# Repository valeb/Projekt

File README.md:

Projekt
=======

Maturaprojekt von Valetnin Bernard, 5AEL Gewerbeoberschule Meran, SJ 2013/14
Alarmanlage mit RFID-Deaktivierung

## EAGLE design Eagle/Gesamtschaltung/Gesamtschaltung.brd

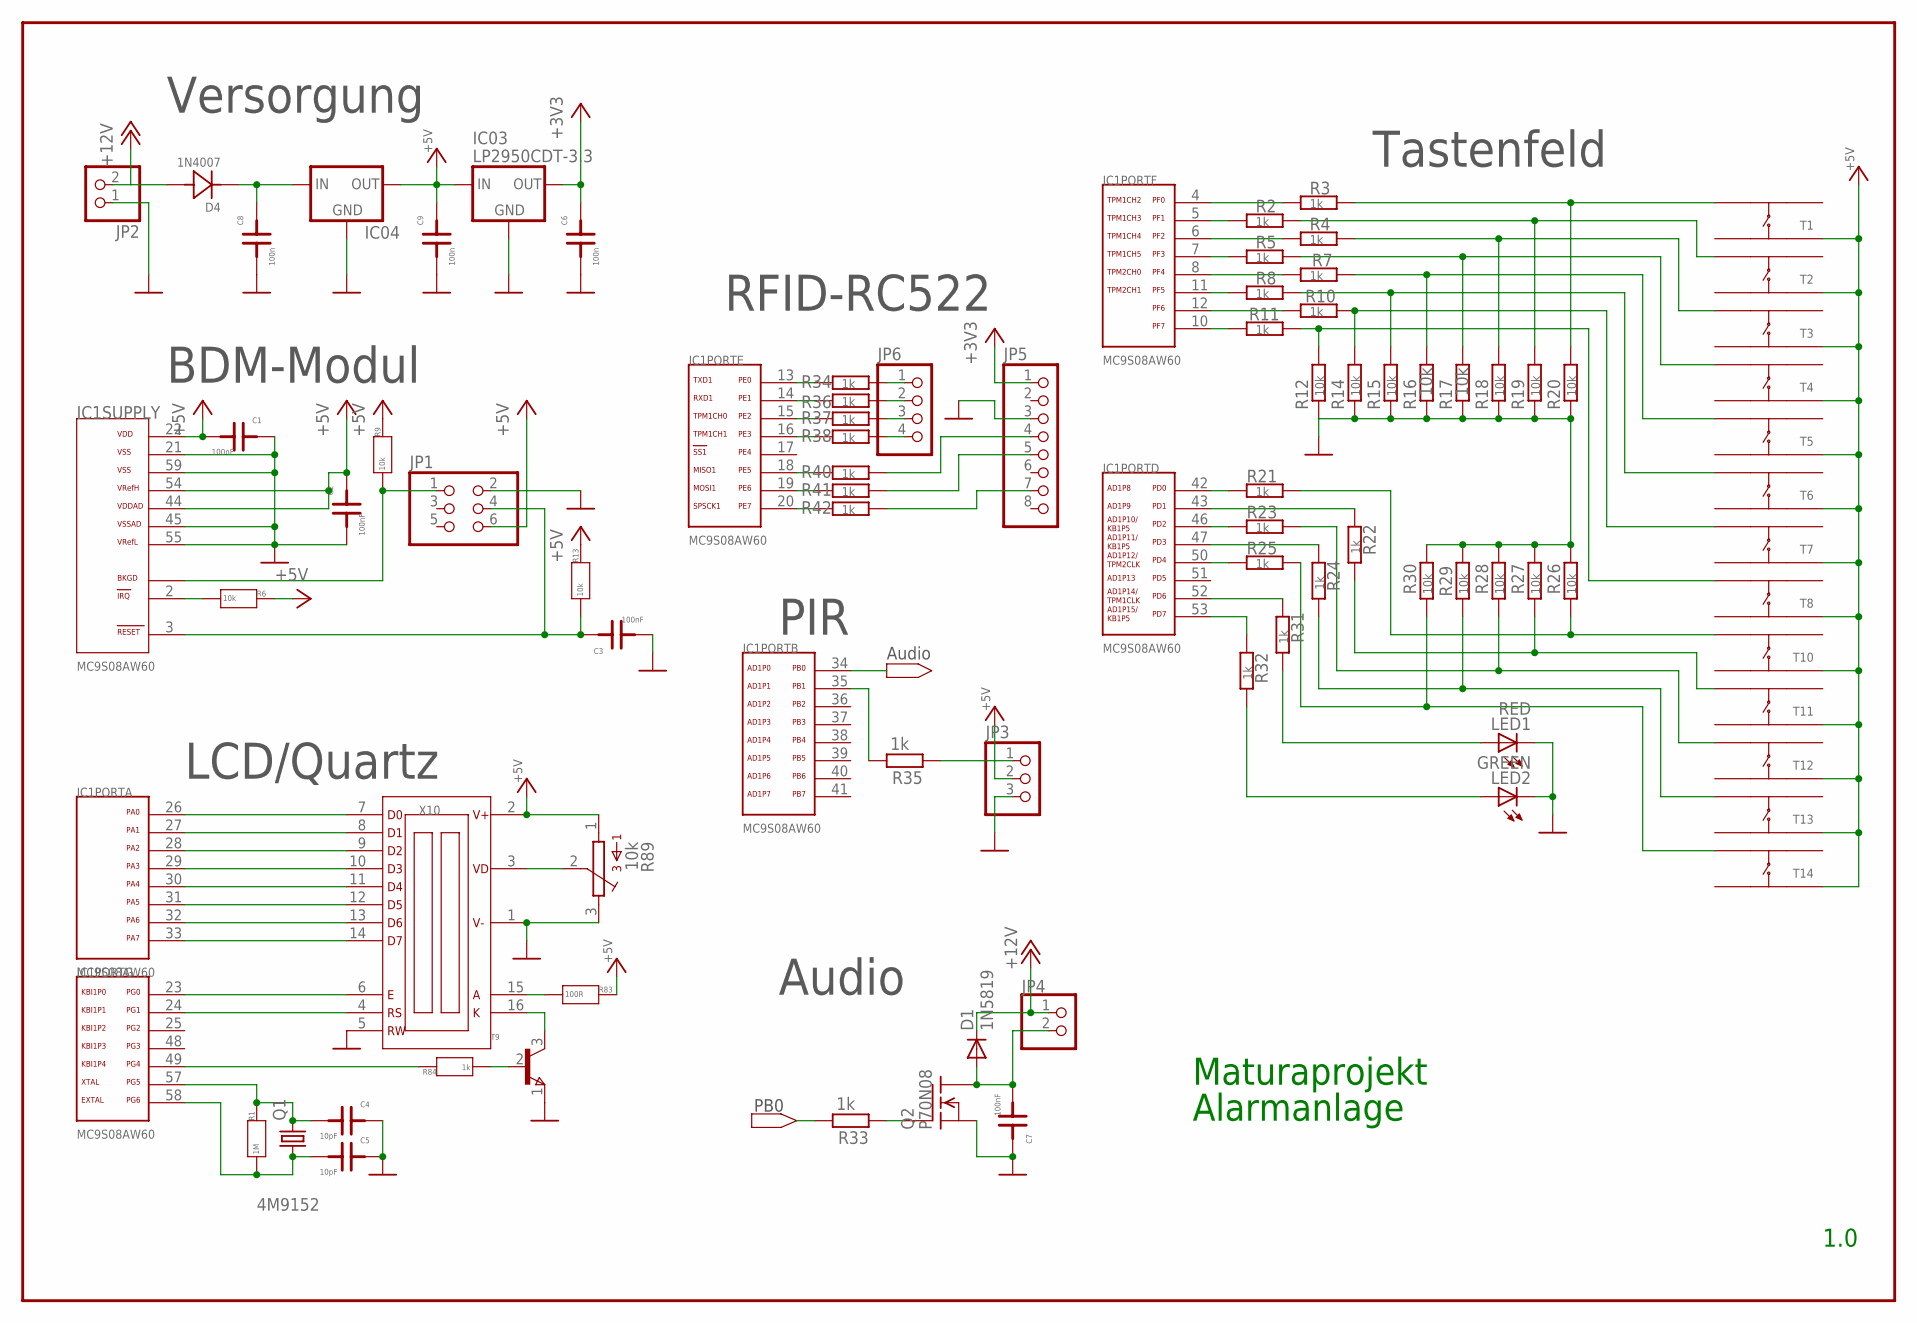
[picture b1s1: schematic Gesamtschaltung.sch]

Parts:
C1, C2, C3, C7: 100nF; 0805F
C4, C5: 10pF; 0805F
C6, C8, C9: 100n; 0805F
D1: 1N5819; DO41-10
D4: 1N4007; D400BH
IC1: MC9S08AW60; LQFP64
IC03: LP2950CDT-3.3; DPACK
IC04: 78XXS
JP1: PINHD-2X3; 2X03
JP2, JP4: PINHD-1X2; 1X02
JP3: PINHD-1X3; 1X03
JP5: PINHD-1X8; 1X08
JP6: PINHD-1X4; 1X04
LED1: RED; LED3MM
LED2: GREEN; LED3MM
Q1: 4M9152; HC49UP
Q2: P70N08; TO220
R1: 1M; 0805
R2, R3, R4, R5, R7, R8, R10, R11, R21, R22, R23, R24, R25, R34, R35, R36, R37, R38, R40, R41, R42: 1k; M0805
R6, R9, R13: 10k; 0805
R12, R14, R15, R16, R17, R18, R19, R20, R26, R27, R28, R29, R30: 10k; M0805
R31, R32: 1k; R0805
R33: 1k; 0207/10
R83: 100R; 0805
R84: 1k; 0805
R89: 10k; S63X
T1, T2, T3, T4, T5, T6, T7, T8, T10, T11, T12, T13, T14: TASTERTHT; TASTE_THT
T9: BC817; SOT-23
X10: FDCC1602E

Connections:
+3V3: C6.2, IC03.3 (OUT), JP5.1
+5V: C1.1, C2.2, C9.2, IC1.22 (VDD), IC1.44 (VDDAD), IC1.54 (VREFH), IC03.1 (IN), IC04.OUT, JP1.6, JP3.2, R6.2, R9.2, R13.2, R83.2, R89.1, T1.A1, T2.A1, T3.A1, T4.A1, T5.A1, T6.A1, T7.A1, T8.A1, T10.A1, T11.A1, T12.A1, T13.A1, T14.A1, X10.2 (V+)
+12V: D1.C, D4.A, JP2.2, JP4.1
BKGD: IC1.56 (BKGD), JP1.1, R9.1
D0: IC1.26 (PA0), X10.7 (D0)
D1: IC1.27 (PA1), X10.8 (D1)
D2: IC1.28 (PA2), X10.9 (D2)
D3: IC1.29 (PA3), X10.10 (D3)
GND: C1.2, C2.1, C3.1, C4.2, C5.2, C6.1, C7.2, C8.1, C9.1, IC1.21 (VSS), IC1.45 (VSSAD), IC1.55 (VREFL), IC1.59 (VSS2), IC03.4 (GND), IC04.GND, JP1.2, JP2.1, JP3.3, JP5.3, LED1.K (C), LED2.K (C), Q2.3 (S), R12.1, R14.1, R15.1, R16.1, R17.1, R18.1, R19.1, R20.1, R26.2, R27.2, R28.2, R29.2, R30.2, R89.3, T9.1 (E), X10.1 (V-), X10.5 (RW)
IRQ: IC1.2 (IRQ/), R6.1
LCD_LED: IC1.49 (PG4), R84.2
unnamed: C8.2, D4.K, IC04.IN
unnamed: R3.2, R20.2, T1.B2
unnamed: R2.2, R19.2, T2.B2
unnamed: IC1.42 (PD0), R21.1
unnamed: R4.2, R18.2, T3.B2
unnamed: R5.2, R17.2, T4.B2
unnamed: R7.2, R16.2, T5.B2
unnamed: IC1.46 (PD2), R23.1
unnamed: IC1.50 (PD4), R25.1
unnamed: R21.2, R26.1, T10.B2
unnamed: R8.2, R15.2, T6.B2
unnamed: R10.2, R14.2, T7.B2
unnamed: R11.2, R12.2, T8.B2
unnamed: IC1.5 (PF1), R2.1
unnamed: IC1.6 (PF2), R4.1
unnamed: C4.1, IC1.57 (PG5), Q1.2, R1.2
unnamed: IC1.43 (PD1), R22.1
unnamed: IC1.47 (PD3), R24.1
unnamed: R22.2, R27.1, T11.B2
unnamed: IC1.53 (PD7), R32.1
unnamed: IC1.7 (PF3), R5.1
unnamed: C5.1, IC1.58 (PG6), Q1.1, R1.1
unnamed: IC1.8 (PF4), R7.1
unnamed: IC1.11 (PF5), R8.1
unnamed: IC1.12 (PF6), R10.1
unnamed: IC1.10 (PF7), R11.1
unnamed: IC1.4 (PF0), R3.1
unnamed: R24.2, R29.1, T13.B2
unnamed: IC1.52 (PD6), R31.1
unnamed: R23.2, R28.1, T12.B2
unnamed: R25.2, R30.1, T14.B2
unnamed: IC1.13 (PE0), R34.1
unnamed: LED2.A, R32.2
unnamed: LED1.A, R31.2
unnamed: JP5.7, R42.2
unnamed: IC1.34 (PB0), R33.2
unnamed: JP3.1, R35.1
unnamed: JP5.5, R41.2
unnamed: JP5.4, R40.2
unnamed: Q2.1 (G), R33.1
unnamed: IC1.35 (PB1), R35.2
unnamed: IC1.14 (PE1), R36.1
unnamed: IC1.15 (PE2), R37.1
unnamed: IC1.16 (PE3), R38.1
unnamed: JP6.4, R38.2
unnamed: C7.1, D1.A, JP4.2, Q2.2 (D)
unnamed: IC1.18 (PE5), R40.1
unnamed: IC1.19 (PE6), R41.1
unnamed: IC1.30 (PA4), X10.11 (D4)
unnamed: IC1.31 (PA5), X10.12 (D5)
unnamed: IC1.32 (PA6), X10.13 (D6)
unnamed: IC1.33 (PA7), X10.14 (D7)
unnamed: IC1.20 (PE7), R42.1
unnamed: JP6.3, R37.2
unnamed: IC1.23 (PG0), X10.6 (E)
unnamed: JP6.2, R36.2
unnamed: JP6.1, R34.2
unnamed: IC1.24 (PG1), X10.4 (RS)
unnamed: R89.2, X10.3 (VD)
unnamed: R83.1, X10.15 (A)
unnamed: T9.3 (C), X10.16 (K)
unnamed: R84.1, T9.2 (B)
RESET: C3.2, IC1.3 (RST/), JP1.4, R13.1

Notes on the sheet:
Maturaprojekt
Alarmanlage
1.0
Tastenfeld
Versorgung
BDM-Modul
LCD/Quartz
PIR
RFID-RC522
Audio
PB0

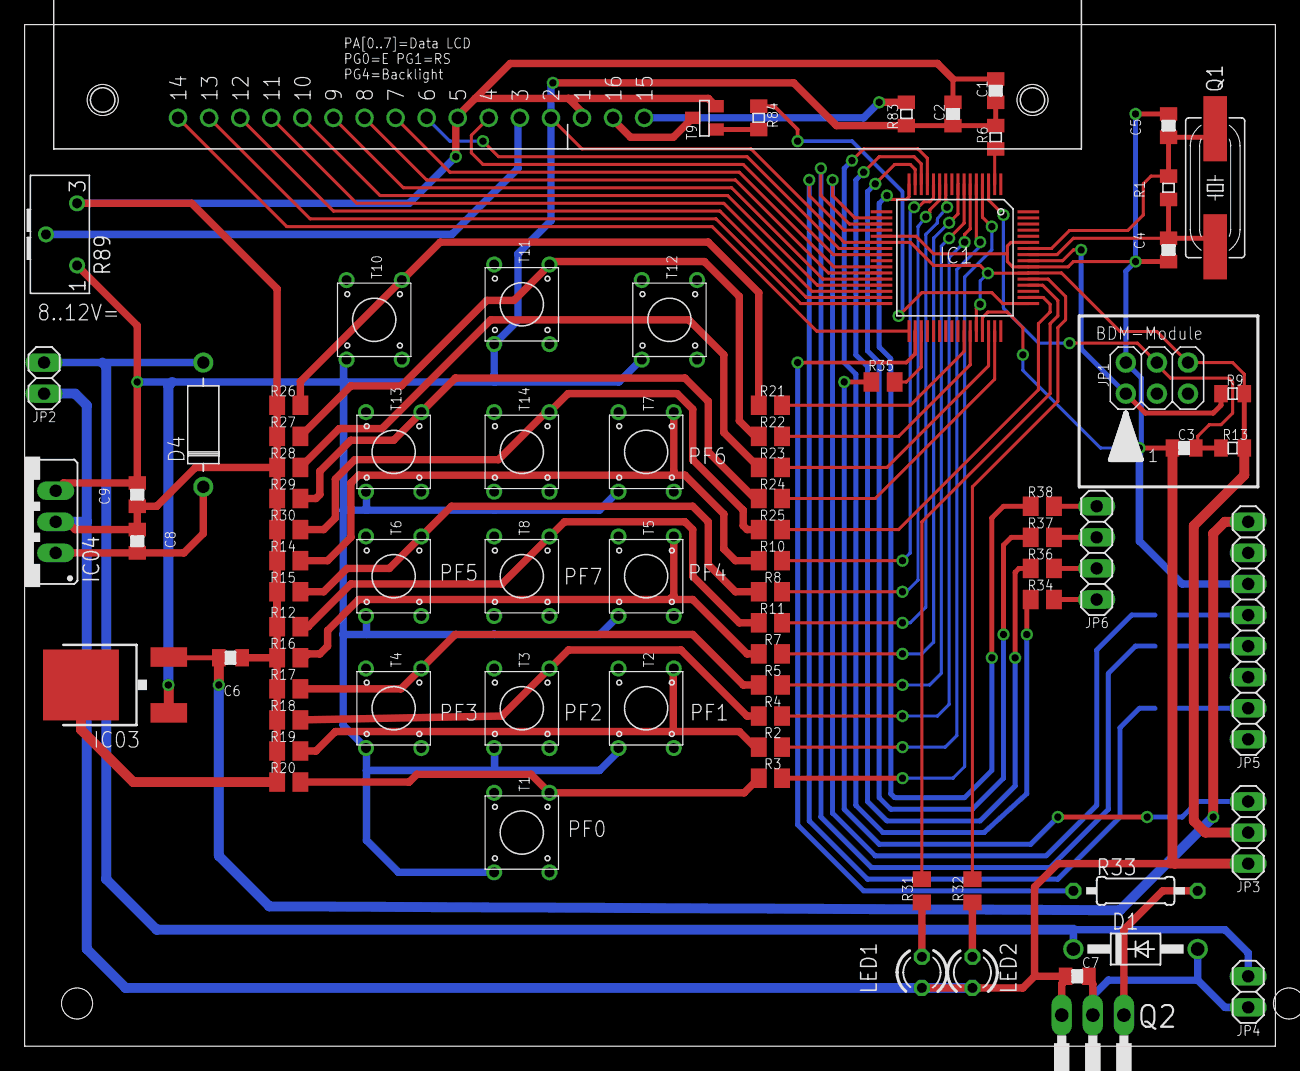
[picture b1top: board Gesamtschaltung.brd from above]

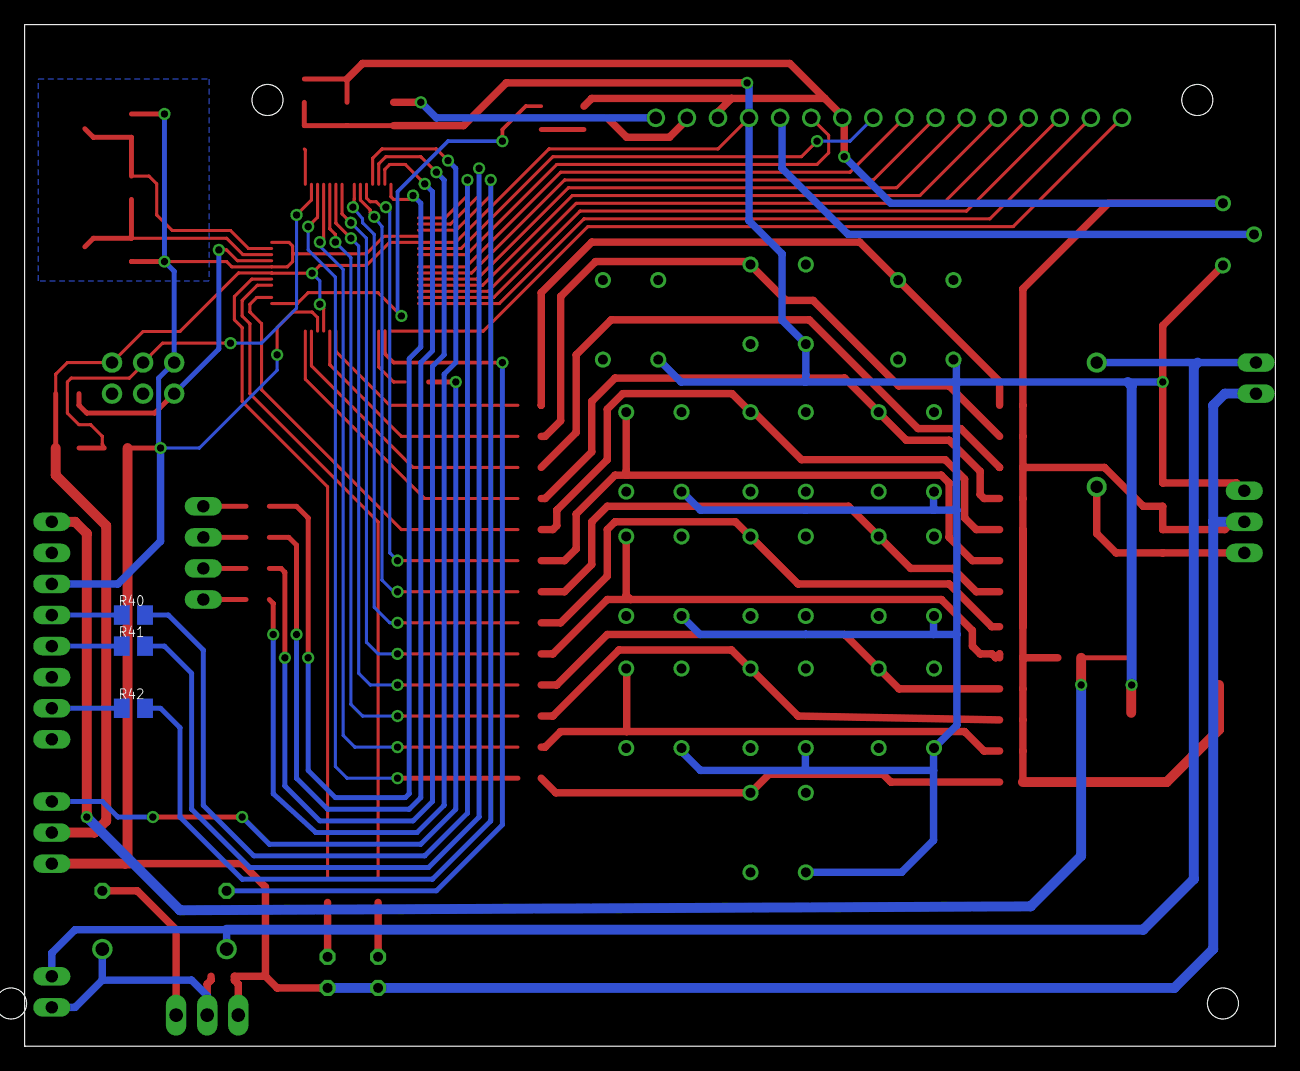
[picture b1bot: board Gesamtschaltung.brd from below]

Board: 2 copper layers, 102.2 x 83.5 mm, 83 parts (3 on the bottom side), 74 nets.

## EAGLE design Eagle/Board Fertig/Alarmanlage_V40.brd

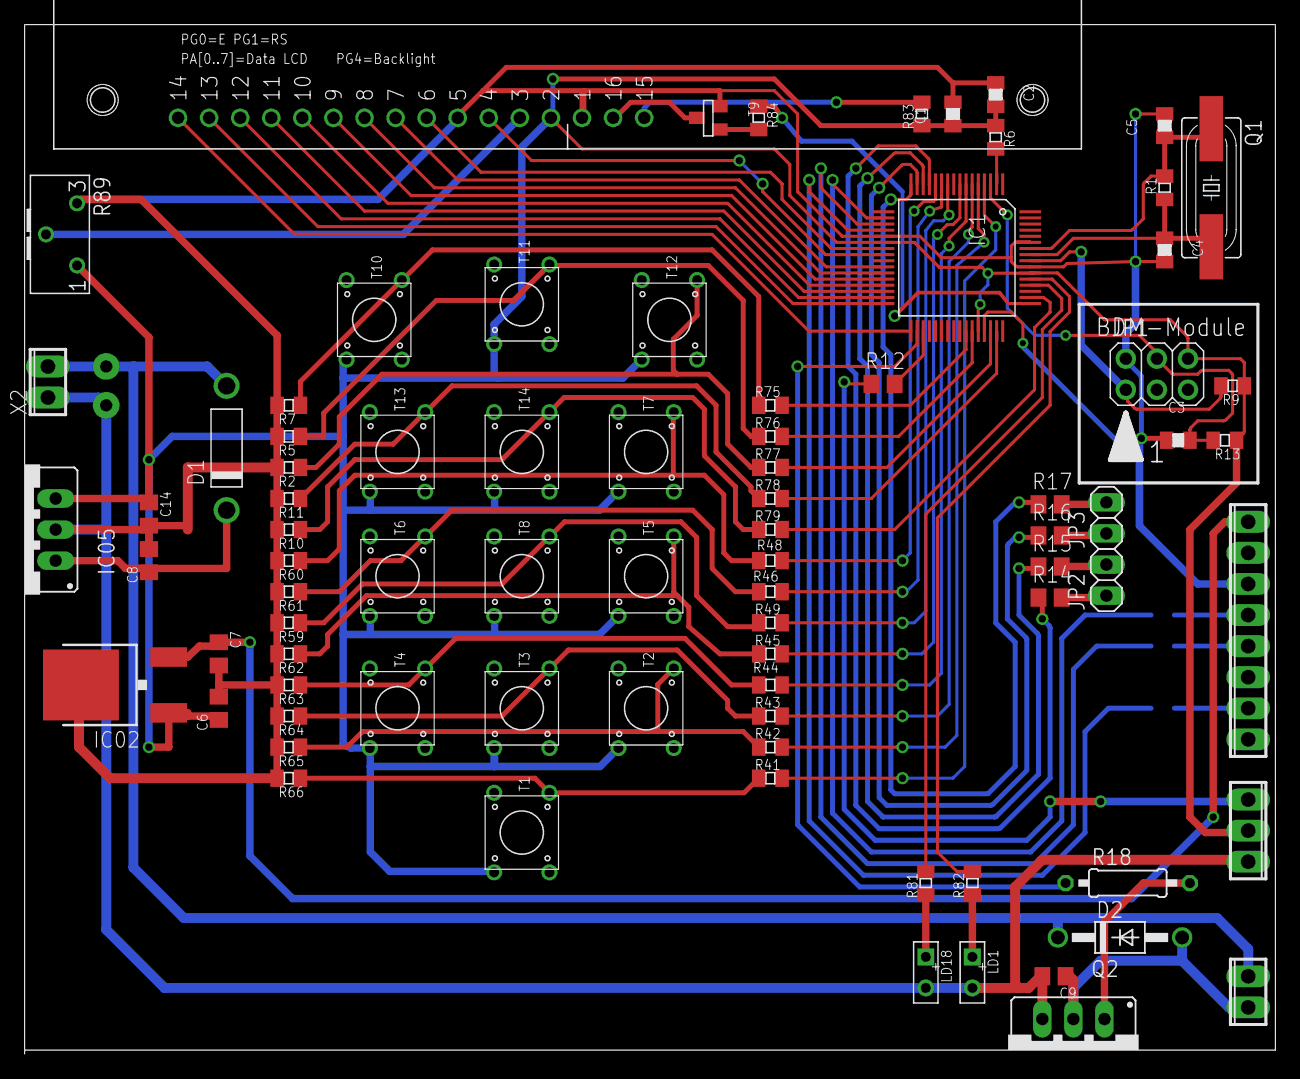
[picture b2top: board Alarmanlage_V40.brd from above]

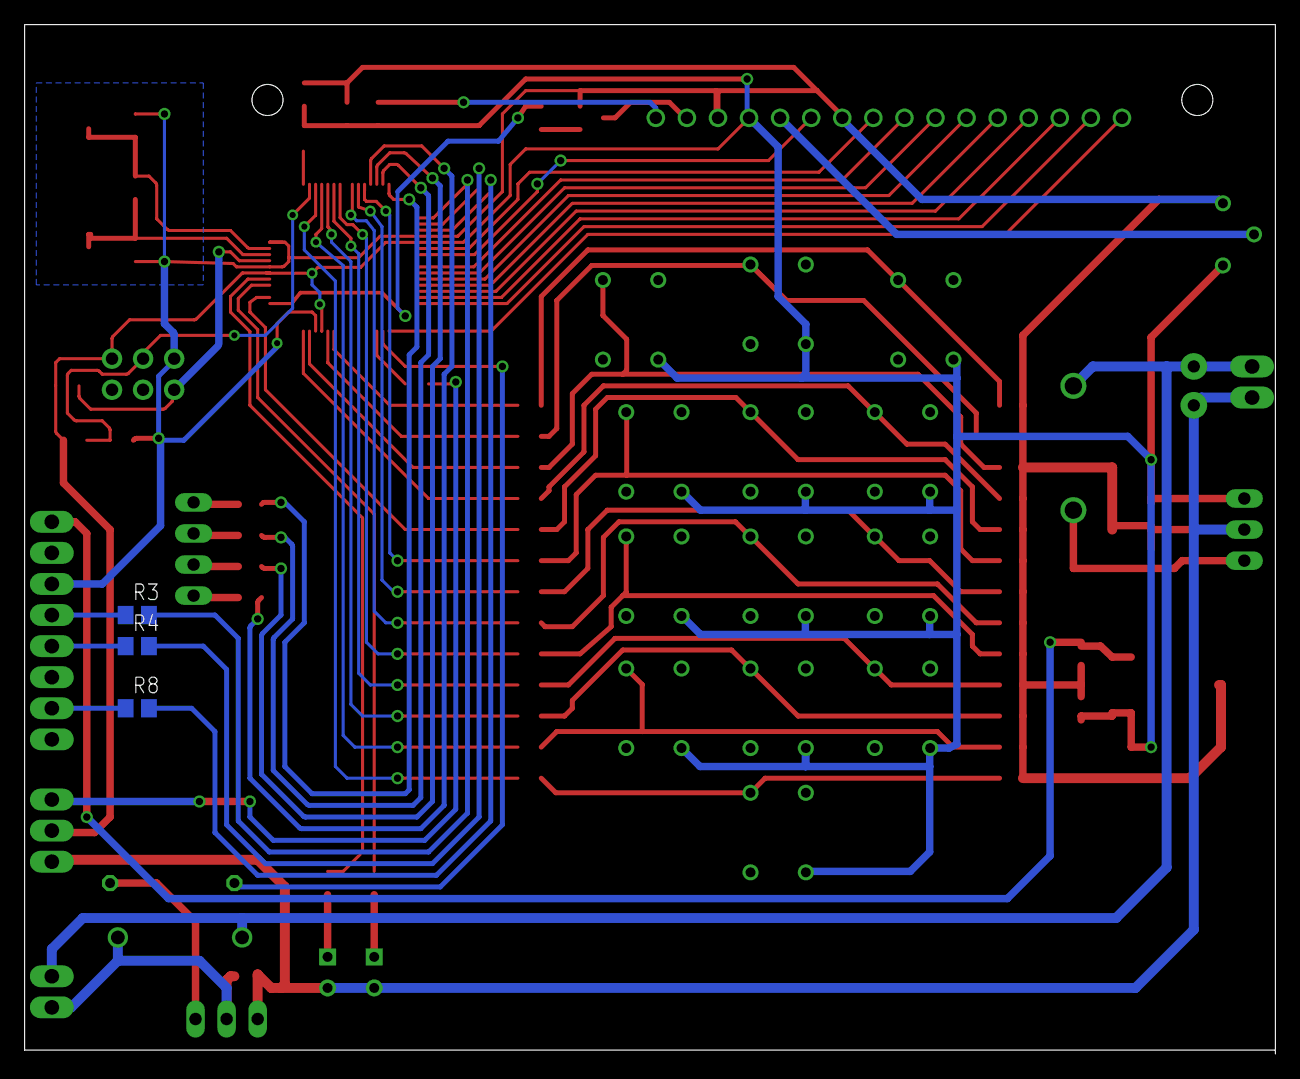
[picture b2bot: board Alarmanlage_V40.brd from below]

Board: 2 copper layers, 102.2 x 83.8 mm, 85 parts (3 on the bottom side), 74 nets.

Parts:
C1, C2, C3: 100nF; 0805F
C4, C5: 10pF; 0805F
C6, C8: 330nF; C0805
C7, C9, C14: 100nF; C0805
D1: 1N4007; DO201
D2: 1N4004; DO41-10
IC1: MC9S08AW60; LQFP64
IC02: 3.3V; DPACK
IC05: 5V; TO-220_V
JP1: 2X03
JP2, JP3: 1X02
LD1: GREEN; LED2X5MM
LD18: RED; LED2X5MM
Q1: 4M9152; HC49UP
Q2: P5N50D; TO-220_V
R1: 1M; 0805
R2, R5, R6, R7, R9, R10, R11, R13, R59, R60, R61, R62, R63, R64, R65, R66: 10k; 0805
R3, R4, R8: R0805
R12, R14, R15, R16, R17: 1k; R0805
R18: 0207/10
R41, R42, R43, R44, R45, R46, R48, R49, R75, R76, R77, R78, R79, R81, R82, R84: 1k; 0805
R83: 100R; 0805
R89: 10k; S63X
T1, T2, T3, T4, T5, T6, T7, T8, T10, T11, T12, T13, T14: TASTE_THT
T9: SOT-23
X1: 8POL254
X2, X3: 2POL254
X4: 3POL254
X10: FDCC1602E

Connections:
+3V3: C7.1, IC02.3, X1.8
+5V: C1.1, C2.2, C6.1, C14.1, IC1.22, IC1.44, IC1.54, IC02.1, IC05.OUT, JP1.6, R6.2, R9.2, R13.2, R83.2, R89.1, T1.A1, T2.A1, T3.A1, T4.A1, T5.A1, T6.A1, T7.A1, T8.A1, T10.A1, T11.A1, T12.A1, T13.A1, T14.A1, X4.2, X10.2
+12V: D1.A, D2.C, X2.2, X3.2
BKGD: IC1.56, JP1.1, R9.1
D0: IC1.26, X10.7
D1: IC1.27, X10.8
D2: IC1.28, X10.9
D3: IC1.29, X10.10
GND: C1.2, C2.1, C3.1, C4.2, C5.2, C6.2, C7.2, C8.2, C9.2, C14.2, IC1.21, IC1.45, IC1.55, IC1.59, IC02.4, IC05.GND, JP1.2, LD1.1, LD18.1, Q2.OUT, R2.1, R5.1, R7.1, R10.1, R11.1, R59.1, R60.1, R61.1, R62.1, R63.1, R64.1, R65.1, R66.1, R89.3, T9.1, X1.6, X2.1, X4.3, X10.1, X10.5
IRQ: IC1.2, R6.1
LCD_LED: IC1.49, R84.2
unnamed: R3.2, X1.5
unnamed: C8.1, D1.K, IC05.IN
unnamed: IC1.20, R8.1
unnamed: IC1.42, R75.1
unnamed: IC1.19, R4.1
unnamed: IC1.18, R3.1
unnamed: IC1.43, R76.1
unnamed: IC1.46, R77.1
unnamed: IC1.47, R78.1
unnamed: R49.2, R59.2, T8.B2
unnamed: IC1.50, R79.1
unnamed: R7.2, R75.2, T10.B2
unnamed: R4.2, X1.4
unnamed: C4.1, IC1.57, Q1.2, R1.2
unnamed: IC1.52, R81.1
unnamed: IC1.53, R82.1
unnamed: R8.2, X1.2
unnamed: R5.2, R76.2, T11.B2
unnamed: IC1.12, R48.1
unnamed: C5.1, IC1.58, Q1.1, R1.1
unnamed: IC1.11, R46.1
unnamed: IC1.4, R41.1
unnamed: R12.2, X4.1
unnamed: LD1.2, R82.2
unnamed: IC1.13, R14.2
unnamed: C9.1, D2.A, Q2.GND, X3.1
unnamed: R11.2, R78.2, T13.B2
unnamed: LD18.2, R81.2
unnamed: IC1.35, R12.1
unnamed: IC1.14, R15.2
unnamed: R10.2, R79.2, T14.B2
unnamed: IC1.15, R16.2
unnamed: R45.2, R62.2, T5.B2
unnamed: IC1.34, R18.1
unnamed: R48.2, R60.2, T7.B2
unnamed: IC1.16, R17.2
unnamed: JP2.1, R14.1
unnamed: JP2.2, R15.1
unnamed: JP3.1, R16.1
unnamed: IC1.10, R49.1
unnamed: JP3.2, R17.1
unnamed: Q2.IN, R18.2
unnamed: IC1.5, R42.1
unnamed: IC1.6, R43.1
unnamed: IC1.7, R44.1
unnamed: IC1.8, R45.1
unnamed: IC1.30, X10.11
unnamed: IC1.31, X10.12
unnamed: IC1.32, X10.13
unnamed: IC1.33, X10.14
unnamed: IC1.23, X10.6
unnamed: IC1.24, X10.4
unnamed: R89.2, X10.3
unnamed: R46.2, R61.2, T6.B2
unnamed: R44.2, R63.2, T4.B2
unnamed: R43.2, R64.2, T3.B2
unnamed: R42.2, R65.2, T2.B2
unnamed: R41.2, R66.2, T1.B2
unnamed: R2.2, R77.2, T12.B2
unnamed: R83.1, X10.15
unnamed: T9.3, X10.16
unnamed: R84.1, T9.2
RESET: C3.2, IC1.3, JP1.4, R13.1

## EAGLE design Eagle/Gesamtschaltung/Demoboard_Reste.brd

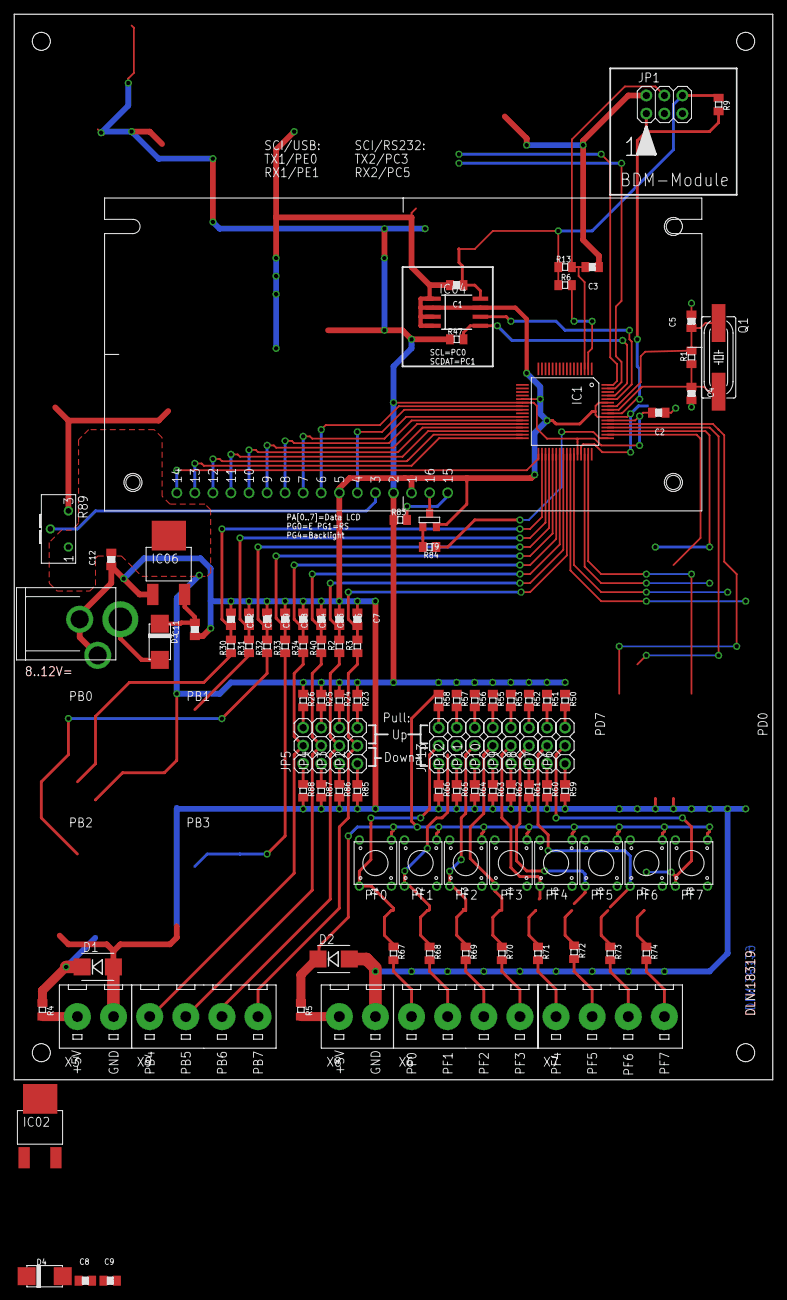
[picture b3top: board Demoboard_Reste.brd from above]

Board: 2 copper layers, 106.7 x 149.9 mm, 105 parts (0 on the bottom side), 81 nets.

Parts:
C1, C2, C3: 100nF; 0805F
C4, C5: 10pF; 0805F
C6, C7, C13, C14, C18, C19, C21, C22: 10nF; 0805F
C8, C9, C11, C12: 1µF; 0805F
D1, D2: SA5.0CA; SMB
D3, D4: 1N4007; MELF_B
IC1: MC9S08AW60; LQFP64
IC02, IC06: LM1117-5.0; DPAK
IC04: 24LC256; SO-08M
JP1: 2X03
JP2, JP3, JP4, JP5, JP6, JP7, JP8, JP9, JP10, JP11, JP12, JP13: 1X03
Q1: 4M9152; HC49UP
R1: 1M; 0805
R2, R3, R6, R9, R13, R23, R24, R25, R26, R30, R31, R32, R33, R34, R40, R50, R51, R52, R53, R55, R56, R57, R58, R59, R60, R61, R62, R63, R64, R65, R66, R85, R86, R87, R88: 10k; 0805
R4, R5: 27R; 0805
R47: 680R; 0805
R67, R68, R69, R70, R71, R72, R73, R74, R83: 100R; 0805
R84: 1k; 0805
R89: 10k; S63X
T1, T2, T3, T4, T5, T6, T7, T8: TASTE_THT
T9: SOT-23
X3, X8: KLEMME2
X4: SPP
X6, X7, X9: KLEMME4
X10: FDCC1602E

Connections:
+5V: C1.1, C2.2, C9.2, C12.2, D1.C, D2.C, IC1.22, IC1.44, IC1.54, IC02.4, IC04.8, IC06.4, JP1.6, R4.2, R5.2, R6.2, R9.2, R13.2, R23.2, R24.2, R25.2, R26.2, R47.2, R83.2, R89.1, T1.A1, T2.A1, T3.A1, T4.A1, T5.A1, T6.A1, T7.A1, T8.A1, X10.2
ADCPB0: C22.2, IC1.34, R30.1
ADCPB1: C21.2, IC1.35, R31.1
ADCPB2: C19.2, IC1.36, R32.1
ADCPB3: C18.2, IC1.37, R33.1
ADCPB4: C14.2, IC1.38, R34.1
ADCPB5: C13.2, IC1.39, R40.1
ADCPB6: C6.2, IC1.40, R2.1
ADCPB7: C7.2, IC1.41, R3.1
ANA4: JP5.2, R34.2, X9.1
ANA5: JP4.2, R40.2, X9.2
ANA6: JP3.2, R2.2, X9.3
ANA7: JP2.2, R3.2, X9.4
BKGD: IC1.56, JP1.1, R9.1
D0: IC1.26, X10.7
D1: IC1.27, X10.8
D2: IC1.28, X10.9
D3: IC1.29, X10.10
GND: C1.2, C2.1, C3.1, C4.2, C5.2, C6.1, C7.1, C8.1, C9.1, C11.1, C12.1, C13.1, C14.1, C18.1, C19.1, C21.1, C22.1, D1.A, D2.A, IC1.21, IC1.45, IC1.55, IC1.59, IC02.1, IC04.1, IC04.2, IC04.3, IC04.4, IC04.7, IC06.1, JP1.2, R59.1, R60.1, R61.1, R62.1, R63.1, R64.1, R65.1, R66.1, R85.1, R86.1, R87.1, R88.1, R89.3, T9.1, X3.2, X4.1, X4.3, X8.2, X10.1, X10.5
IRQ: IC1.2, R6.1
LCD_LED: IC1.49, R84.2
unnamed: C8.2, D4.K, IC02.3
unnamed: JP13.3, R58.1
unnamed: JP12.3, R57.1
unnamed: R69.2, T3.B2
unnamed: C4.1, IC1.57, Q1.2, R1.2
unnamed: C5.1, IC1.58, Q1.1, R1.1
unnamed: JP11.3, R56.1
unnamed: R71.2, T5.B2
unnamed: R72.2, T6.B2
unnamed: R73.2, T7.B2
unnamed: JP10.3, R55.1
unnamed: JP9.3, R53.1
unnamed: JP8.3, R52.1
unnamed: JP7.3, R51.1
unnamed: R5.1, X8.1
unnamed: IC1.30, X10.11
unnamed: IC1.31, X10.12
unnamed: IC1.32, X10.13
unnamed: IC1.33, X10.14
unnamed: R4.1, X3.1
unnamed: R67.2, T1.B2
unnamed: IC1.23, X10.6
unnamed: R68.2, T2.B2
unnamed: JP6.3, R50.1
unnamed: IC1.24, X10.4
unnamed: R70.2, T4.B2
unnamed: R89.2, X10.3
unnamed: JP6.1, R59.2
unnamed: JP7.1, R60.2
unnamed: JP8.1, R61.2
unnamed: JP9.1, R62.2
unnamed: R74.2, T8.B2
unnamed: JP10.1, R63.2
unnamed: JP11.1, R64.2
unnamed: JP12.1, R65.2
unnamed: JP13.1, R66.2
unnamed: C11.2, D3.K, IC06.3
unnamed: D3.A, X4.2
unnamed: R83.1, X10.15
unnamed: T9.3, X10.16
unnamed: R84.1, T9.2
unnamed: JP5.3, R26.1
unnamed: JP4.3, R25.1
unnamed: JP3.3, R24.1
unnamed: JP2.3, R23.1
unnamed: JP2.1, R85.2
unnamed: JP3.1, R86.2
unnamed: JP4.1, R87.2
unnamed: JP5.1, R88.2
PF0: R67.1, X6.1
PF1: R68.1, X6.2
PF2: R69.1, X6.3
PF3: R70.1, X6.4
PF4: R71.1, X7.1
PF5: R72.1, X7.2
PF6: R73.1, X7.3
PF7: R74.1, X7.4
RESET: C3.2, IC1.3, JP1.4, R13.1
SCL: IC1.60, IC04.6
SDA: IC1.61, IC04.5, R47.1

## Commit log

2013-09-08 add Machbarkeitsstudie
2013-09-08 add git cheatsheet
2013-09-15 add Zeichnug, Add Machbarkeitsstudie, add Projektbeschreibung
2013-09-15 Alarm Machbarkeit gelöscht
2013-09-15 Zeichnung.svg geändert
2013-09-15 README.md aktualisiert
2013-09-21 Links erstellt, Machbarkeitsstude geaendert, Projektbeschreibung fertig
2013-09-26 Töne ausgeben.txt erstellt, Machbarkeitsstudie erweitert
2013-09-27 Gantt-Diagramm erstellt
2013-09-29 Gantt-Diagramm aktualisiert
2013-11-03 Gantt-Diagramm beendet, Eagle begonnen (Auio und Versorgung, Bibliothek), Software begonnn
2014-01-07 add Board-Fertig, add Testsoftware
2014-01-07 changed Gantt-Diagramm
2014-01-08 change Gant-Diagramm, add Board_fertig
2014-01-08 Board. Gantt, Software
2014-01-10 add Blinklichter, Menue, Tastenrouteine to Gesamtprogramm
2014-01-12 mod SW_AW32_Alarmanlage_V10: add Passwort, add Bewegungsmelder, add Alarton; mod Gantt-Diagramm.ods
2014-01-20 add Timerinterrupt.inc, mod Folders, mod Ganttdiagramm, del Ganttdiagramm.docx
2014-01-29 add Frequenzen-Berechner, mod Alarm_Test
2014-01-30 mod Timerinterrupt_V10
2014-02-02 finish Alarm_Testsoftware, mod Gesamtprogramm (add Timerinterrupt_V20.inc, mod Alarmton.inc), mod Ganttdiagramm
2014-02-03 add Gesamtprogramm_V20, RealTime auf Timer 1 Channel 0
2014-02-09 add Testsoftware/Bewegungsmelder, mod Gesamtsoftware_V20: mod Bewegungsmelder.inc
2014-02-20 shit
2014-02-23 mod Geamtwoftware_V20: add Tatenreutine, alle Tasten
2014-02-24 add RFID-Regs
2014-03-05 Commit unter Ubuntu
2014-03-06 Add Bilder-Ordner
2014-03-06 mod RFID, still nor working
2014-03-06 add Version 3.0, include RFID, still doesnt work, fix Rechtschreibfehler
2014-03-10 mod Gesamtporogramm_V30, RFID doesnt work
2014-03-21 mod Gesamtprogramm_V30: fix 'Can't find ASM-Layout', mod RFID_Test, still doesnt work properly
2014-03-27 mod RFID, add Dokumentation, add Befehlsliste, RFID still doesn't work
2014-03-27 add Ports
2014-03-28 mod RFID, might work
2014-03-28 mot Passwort
2014-03-29 mod Passwort, funktioniert, Text nicht angezeigt
2014-03-29 mod Passwort, finktioniert fix eingegeben
2014-04-03 [func] Passwort anderderbar
2014-04-25 func PW_Change
2014-04-25 add 3DDrawings, func PW_Change
2014-04-26 func RFID-Test, Read-Write, RFID not working
2014-04-27 exp Dokumentation, 9 pages now
2014-05-02 add Board
2014-05-04 edit Dokumentation, add diverse Bilder
2014-05-08 add bilder Schaltung, add Bauteilliste, add Bild MosFet, extend Dokumentation
2014-05-15 Fertiiiiiigg
